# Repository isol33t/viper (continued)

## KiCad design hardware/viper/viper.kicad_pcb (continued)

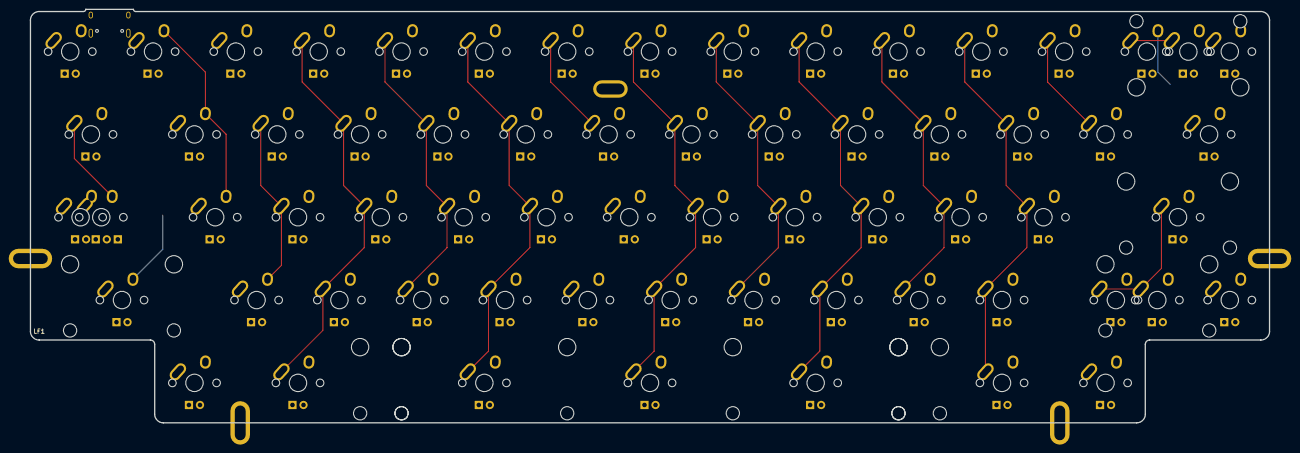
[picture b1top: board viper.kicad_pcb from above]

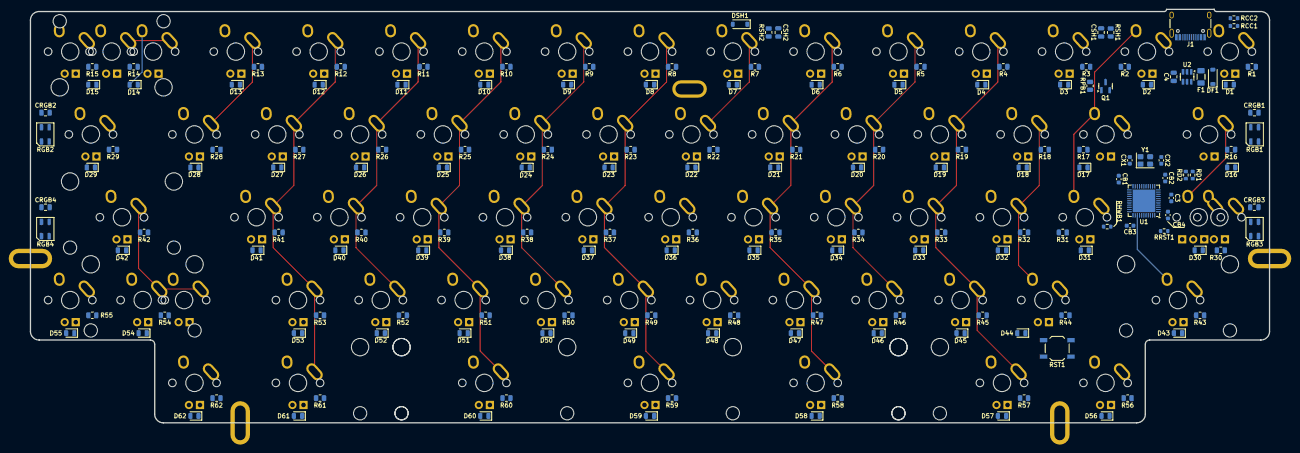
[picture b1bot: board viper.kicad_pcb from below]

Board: 2 copper layers, 285.0 x 95.1 mm, 309 parts (160 on the bottom side), 171 nets.

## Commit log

2025-05-17 init automated viper build
2025-05-17 Import KLE layout & added README notes
2025-05-17 Include via layout & generated collapsed kle layout based on viper_v1_via_url.txt
2025-05-17 Updated README & Dockerfile, included initial output
2025-05-17 format keyboard-layout-via.json
2025-05-17 KLE layout with stepped caps
2025-05-17 Add updated export with stepped caps
2025-05-17 Updated README with RAW data & screenshots
2025-05-17 converted collapsed layout to kle_internal format for kle2netlist
2025-05-18 kle2netlist with layout & netlist xml
2025-05-20 fixed kle layout columns
2025-05-26 Updated kle layout
2025-05-26 MX Hybrid PCB, diode alignment is strange
2025-05-28 converted switch/diode symbols to resistors/leds in generated schematic
2025-05-28 use example diode placement
2025-06-02 updated gitignore
2025-06-04 hell yea
2025-06-04 YAKE - YET ANOTHER KEYBOARD EXPORT
2025-06-05 Added LED matrix & RGB LEDs
2025-06-05 Placed parts with respect to SW1
2025-06-05 Removed ISO enter & Added Split HHKB bottom row
2025-06-06 and the story continues
2025-06-06 Removed Split Left Shift, included ANSI & Split HHKB Presets in VIA spec
2025-06-06 Improved README, restructured repo
    Restructured repo
2025-06-06 kle2netlist docker output + atmega template & split-hhkb attempt
2025-06-06 Import KLE layout & added README notes
    Include via layout & generated collapsed kle layout based on viper_v1_via_url.txt
    Updated README & Dockerfile, included initial output
    format keyboard-layout-via.json
    KLE layout with stepped caps
    Add updated export with stepped caps
    Updated README with RAW data & screenshots
2025-06-06 Merg hardware/viper from dev to main
2025-06-06 Fix path in Dockerfile & remove SOD123 ref, will stick with 0805 for prototype
2025-06-06 Included schematic.svg in README
    Removed DNP flags
2025-06-06 Add notes & licence
2025-06-10 Updated docs
    Updated schematic & changed DSOD123F to 0805 footprints where needed
2025-06-10 Set value for TVS diode + fuse, keep ERC warning just in case
2025-06-10 Attach CAPS_LED
2025-06-10 Manually corrected split-hhkb layout
2025-06-10 Add unrouted renders & updated schematic
2025-06-13 KLE layout for split hhkb + 10u
    Added layout2ledschematic patch with some notes
    Remove old KLE layouts
2025-06-15 Test with voyager60 pinout & kle2netlist
    Mock positions for rgb leds & ferrite bead
    Unrouted board with kle2netlist & pos2orient
    No per-switch leds yet
    Append docker build to existing schematic
    Update schematic from PCB
    Apply pos2orient file
2025-06-16 Reannotated IC/USB resistors
2025-06-16 Imported JP60 board rules & settings
2025-06-16 Included Cimos/KiCad-CustomDesignRules submodule with symlink to jlcpcb design rules
2025-06-16 Improved schematic
2025-06-17 Updated BOM
    Start with manufacturing files.
2025-06-17 Cleaned up WS2812B-Mini 3535 footprint
2025-06-17 Updated README with schematic exports
2025-06-22 Debugging footprints for cleaner DRC
    Set soldermask properties & improved ref placement on back silkscreen
    Silkscreen ref placement & forked HRO type-c receptacle due to edge cut
    Flipping switches
